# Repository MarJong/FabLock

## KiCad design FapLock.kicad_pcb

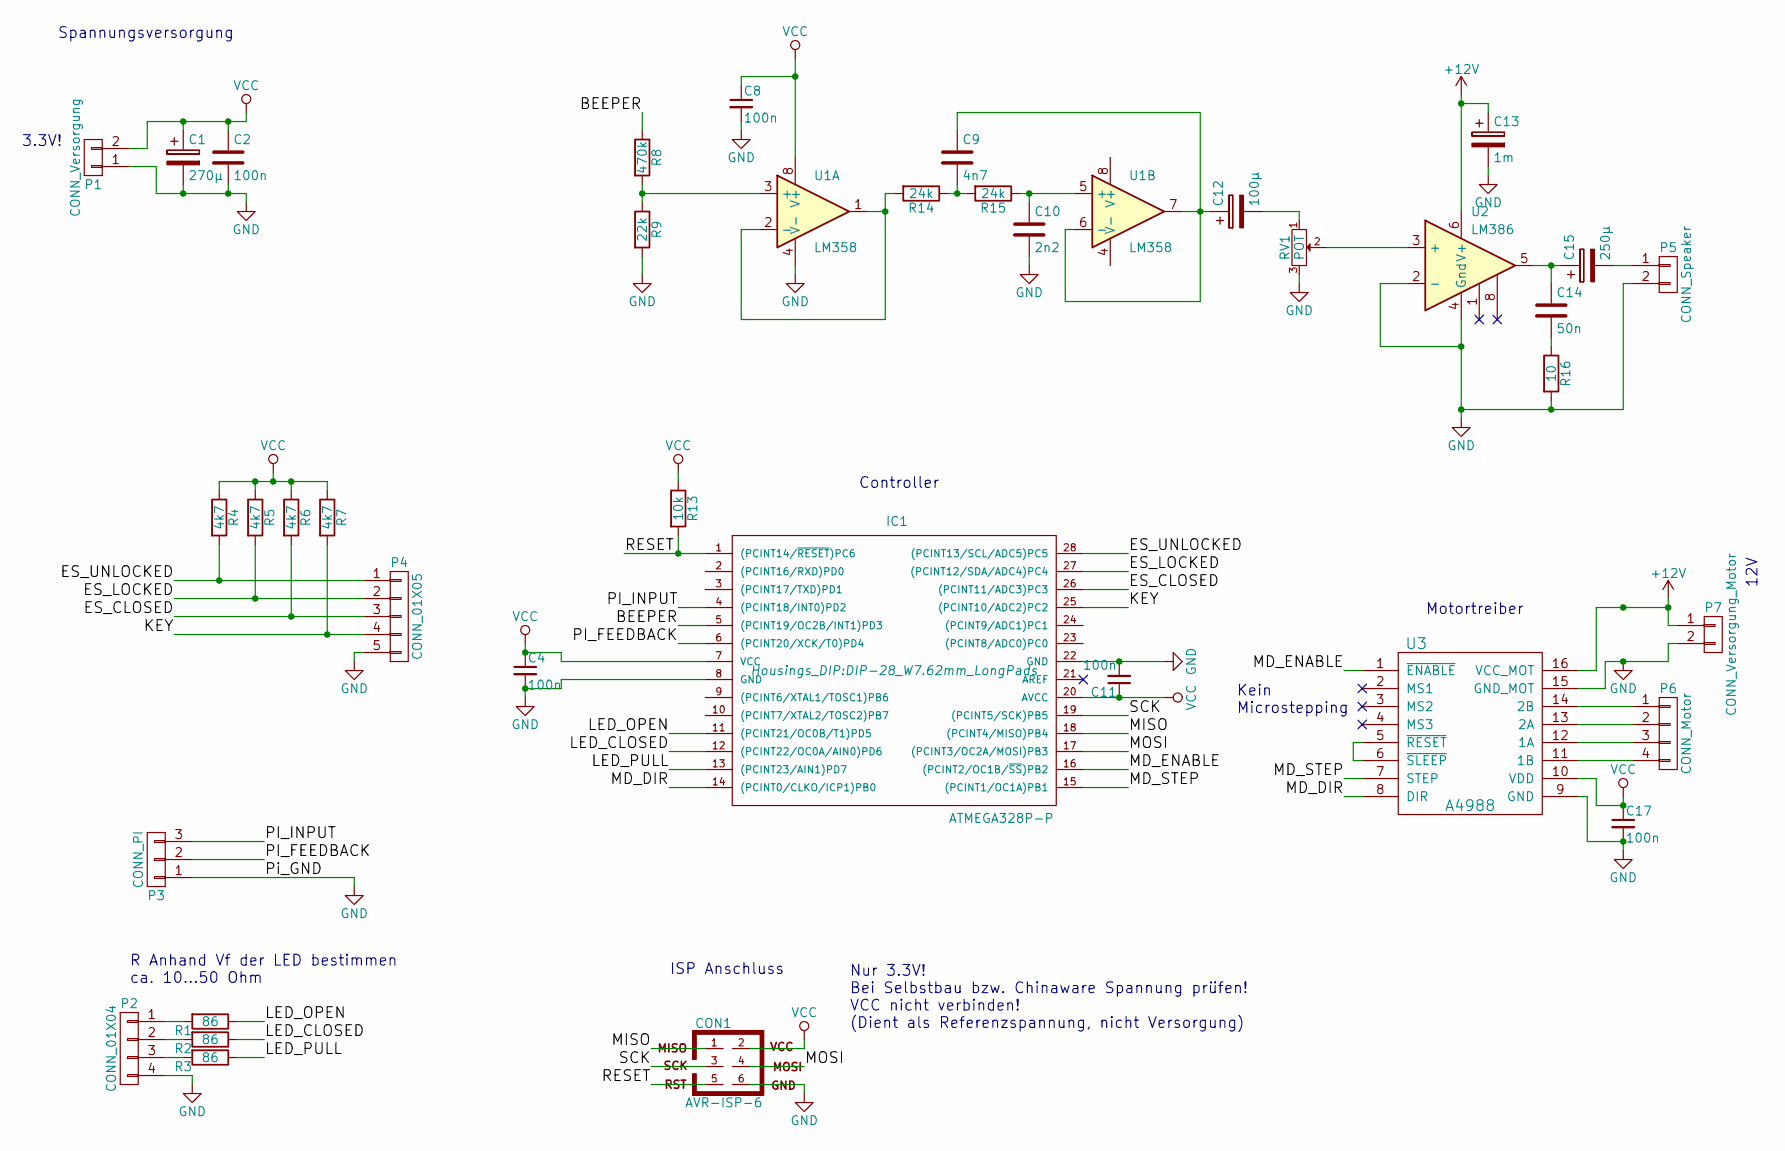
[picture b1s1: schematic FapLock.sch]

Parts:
C1: 270µ; C1V8
C2, C4, C8, C11, C17: 100n; C_Disc_D3_P2.5
C9: 4n7; C_Disc_D3_P2.5
C10: 2n2; C_Disc_D3_P2.5
C12: 100µ; C1V8
C13: 1m; C2V8
C14: 50n; C_Disc_D3_P2.5
C15: 250µ; C1V8
CON1: AVR-ISP-6; Pin_Header_Straight_2x03
IC1: ATMEGA328P-P; DIP-28_W7.62mm_LongPads
P1: CONN_Versorgung; Pin_Header_Straight_1x02
P2: CONN_01X04; Pin_Header_Straight_1x04
P3: CONN_PI; Pin_Header_Straight_1x03
P4: CONN_01X05; Pin_Header_Straight_1x05
P5: CONN_Speaker; Pin_Header_Straight_1x02
P6: CONN_Motor; Pin_Header_Straight_1x04
P7: CONN_Versorgung_Motor; Pin_Header_Straight_1x02
R1, R2, R3: 86; R4
R4, R5, R6, R7: 4k7; R4
R8: 470k; R4
R9: 22k; R4
R13: 10k; R4
R14, R15: 24k; R4
R16: 10; R4
RV1: POT; Potentiometer_Bourns_3339P_Angular_ScrewUp
U1: LM358; DIP-8_W7.62mm_LongPads
U2: LM386; DIP-8_W7.62mm_LongPads
U3: A4988; A4988_Pololu

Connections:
+12V: C13.1, P7.1, U2.6 (V+), U3.16 (VCC_MOT)
/BEEPER: IC1.5 ((PCINT19/OC2B/INT1)PD3), R8.1
/ES_CLOSED: IC1.26 ((PCINT11/ADC3)PC3), P4.3, R6.2
/ES_LOCKED: IC1.27 ((PCINT12/SDA/ADC4)PC4), P4.2, R5.2
/ES_UNLOCKED: IC1.28 ((PCINT13/SCL/ADC5)PC5), P4.1, R4.2
/KEY: IC1.25 ((PCINT10/ADC2)PC2), P4.4, R7.2
/LED_CLOSED: IC1.12 ((PCINT22/OC0A/AIN0)PD6), R2.1
/LED_OPEN: IC1.11 ((PCINT21/OC0B/T1)PD5), R1.1
/LED_PULL: IC1.13 ((PCINT23/AIN1)PD7), R3.1
/MD_DIR: IC1.14 ((PCINT0/CLKO/ICP1)PB0), U3.8 (DIR)
/MD_ENABLE: IC1.16 ((PCINT2/OC1B/~SS~)PB2), U3.1 (~ENABLE)
/MD_STEP: IC1.15 ((PCINT1/OC1A)PB1), U3.7 (STEP)
/MISO: CON1.1, IC1.18 ((PCINT4/MISO)PB4)
/MOSI: CON1.4, IC1.17 ((PCINT3/OC2A/MOSI)PB3)
/PI_FEEDBACK: IC1.6 ((PCINT20/XCK/T0)PD4), P3.2
/PI_INPUT: IC1.4 ((PCINT18/INT0)PD2), P3.3
/RESET: CON1.5, IC1.1 ((PCINT14/~RESET~)PC6), R13.2
/SCK: CON1.3, IC1.19 ((PCINT5/SCK)PB5)
GND: C1.2, C2.2, C4.2, C8.2, C10.2, C11.2, C13.2, C17.2, CON1.6, IC1.8 (GND), IC1.22 (GND), P1.1, P2.4, P3.1, P4.5, P5.2, P7.2, R9.2, R16.2, RV1.3, U1.4 (V-), U2.2 (-), U2.4 (Gnd), U3.9 (GND), U3.15 (GND_MOT)
unnamed: C9.2, R14.1, R15.2
unnamed: C10.1, R15.1, U1.5 (+)
unnamed: C9.1, C12.1, U1.6 (-), U1.7
unnamed: C12.2, RV1.1
unnamed: C14.1, C15.1, U2.5
unnamed: C14.2, R16.1
unnamed: C15.2, P5.1
unnamed: P2.1, R1.2
unnamed: P2.2, R2.2
unnamed: P2.3, R3.2
unnamed: P6.1, U3.14 (2B)
unnamed: P6.2, U3.13 (2A)
unnamed: P6.3, U3.12 (1A)
unnamed: P6.4, U3.11 (1B)
unnamed: R8.2, R9.1, U1.3 (+)
unnamed: R14.2, U1.1, U1.2 (-)
unnamed: RV1.2, U2.3 (+)
unnamed: U3.5 (~RESET), U3.6 (~SLEEP)
VCC: C1.1, C2.1, C4.1, C8.1, C11.1, C17.1, CON1.2, IC1.7 (VCC), IC1.20 (AVCC), P1.2, R4.1, R5.1, R6.1, R7.1, R13.1, U1.8 (V+), U3.10 (VDD)

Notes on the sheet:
3.3V!
Spannungsversorgung
ISP Anschluss
Nur 3.3V! Bei Selbstbau bzw. Chinaware Spannung prüfen! VCC nicht verbinden! (Dient als Referenzspannung, nicht Versorgung)
Motortreiber
Controller
Kein Microstepping
R Anhand Vf der LED bestimmen ca. 10...50 Ohm
12V

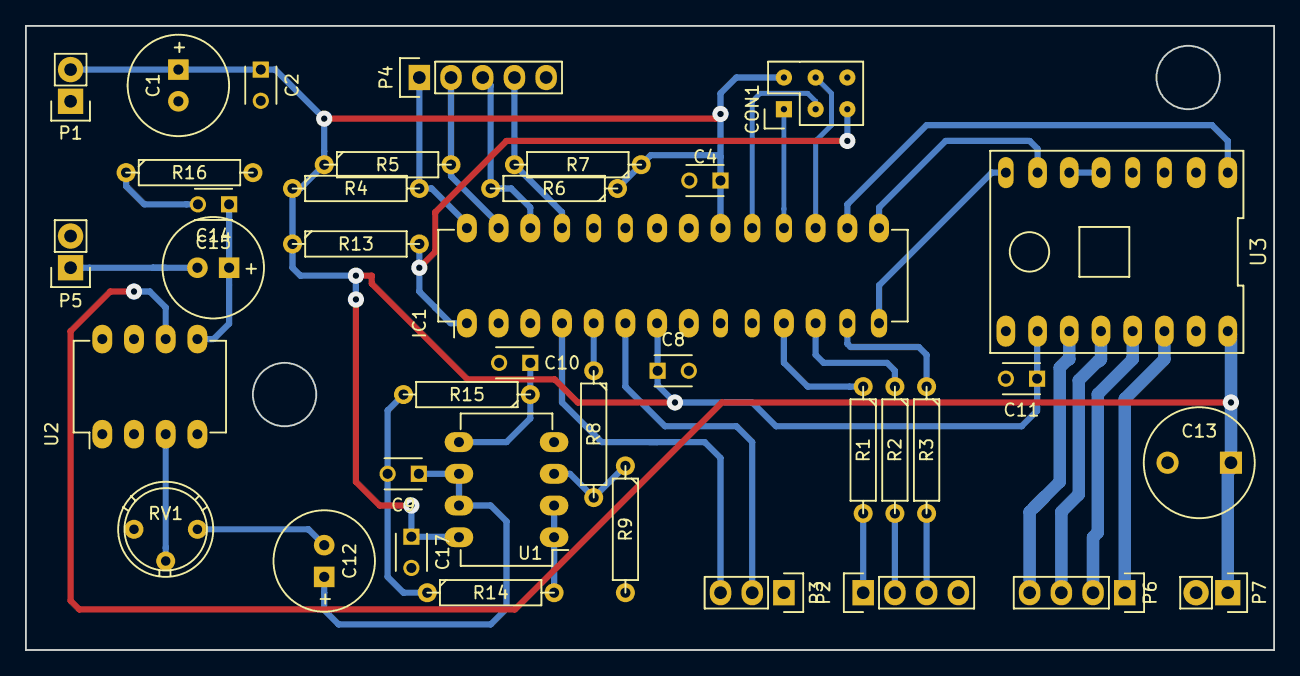
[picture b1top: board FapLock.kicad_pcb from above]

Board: 2 copper layers, 100.0 x 50.0 mm, 38 parts (0 on the bottom side), 38 nets.

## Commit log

2018-01-13 Release
2018-01-13 Audio Fix
